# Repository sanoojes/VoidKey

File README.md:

# VoidKey

A Security key with RP2350A

## PCB

Images will be attached soon

## Firmware

A fork of the [pico-fido](https://github.com/polhenarejos/pico-fido) for this
project [pico-fido-voidkey](https://github.com/sanoojes/pico-fido-voidkey)

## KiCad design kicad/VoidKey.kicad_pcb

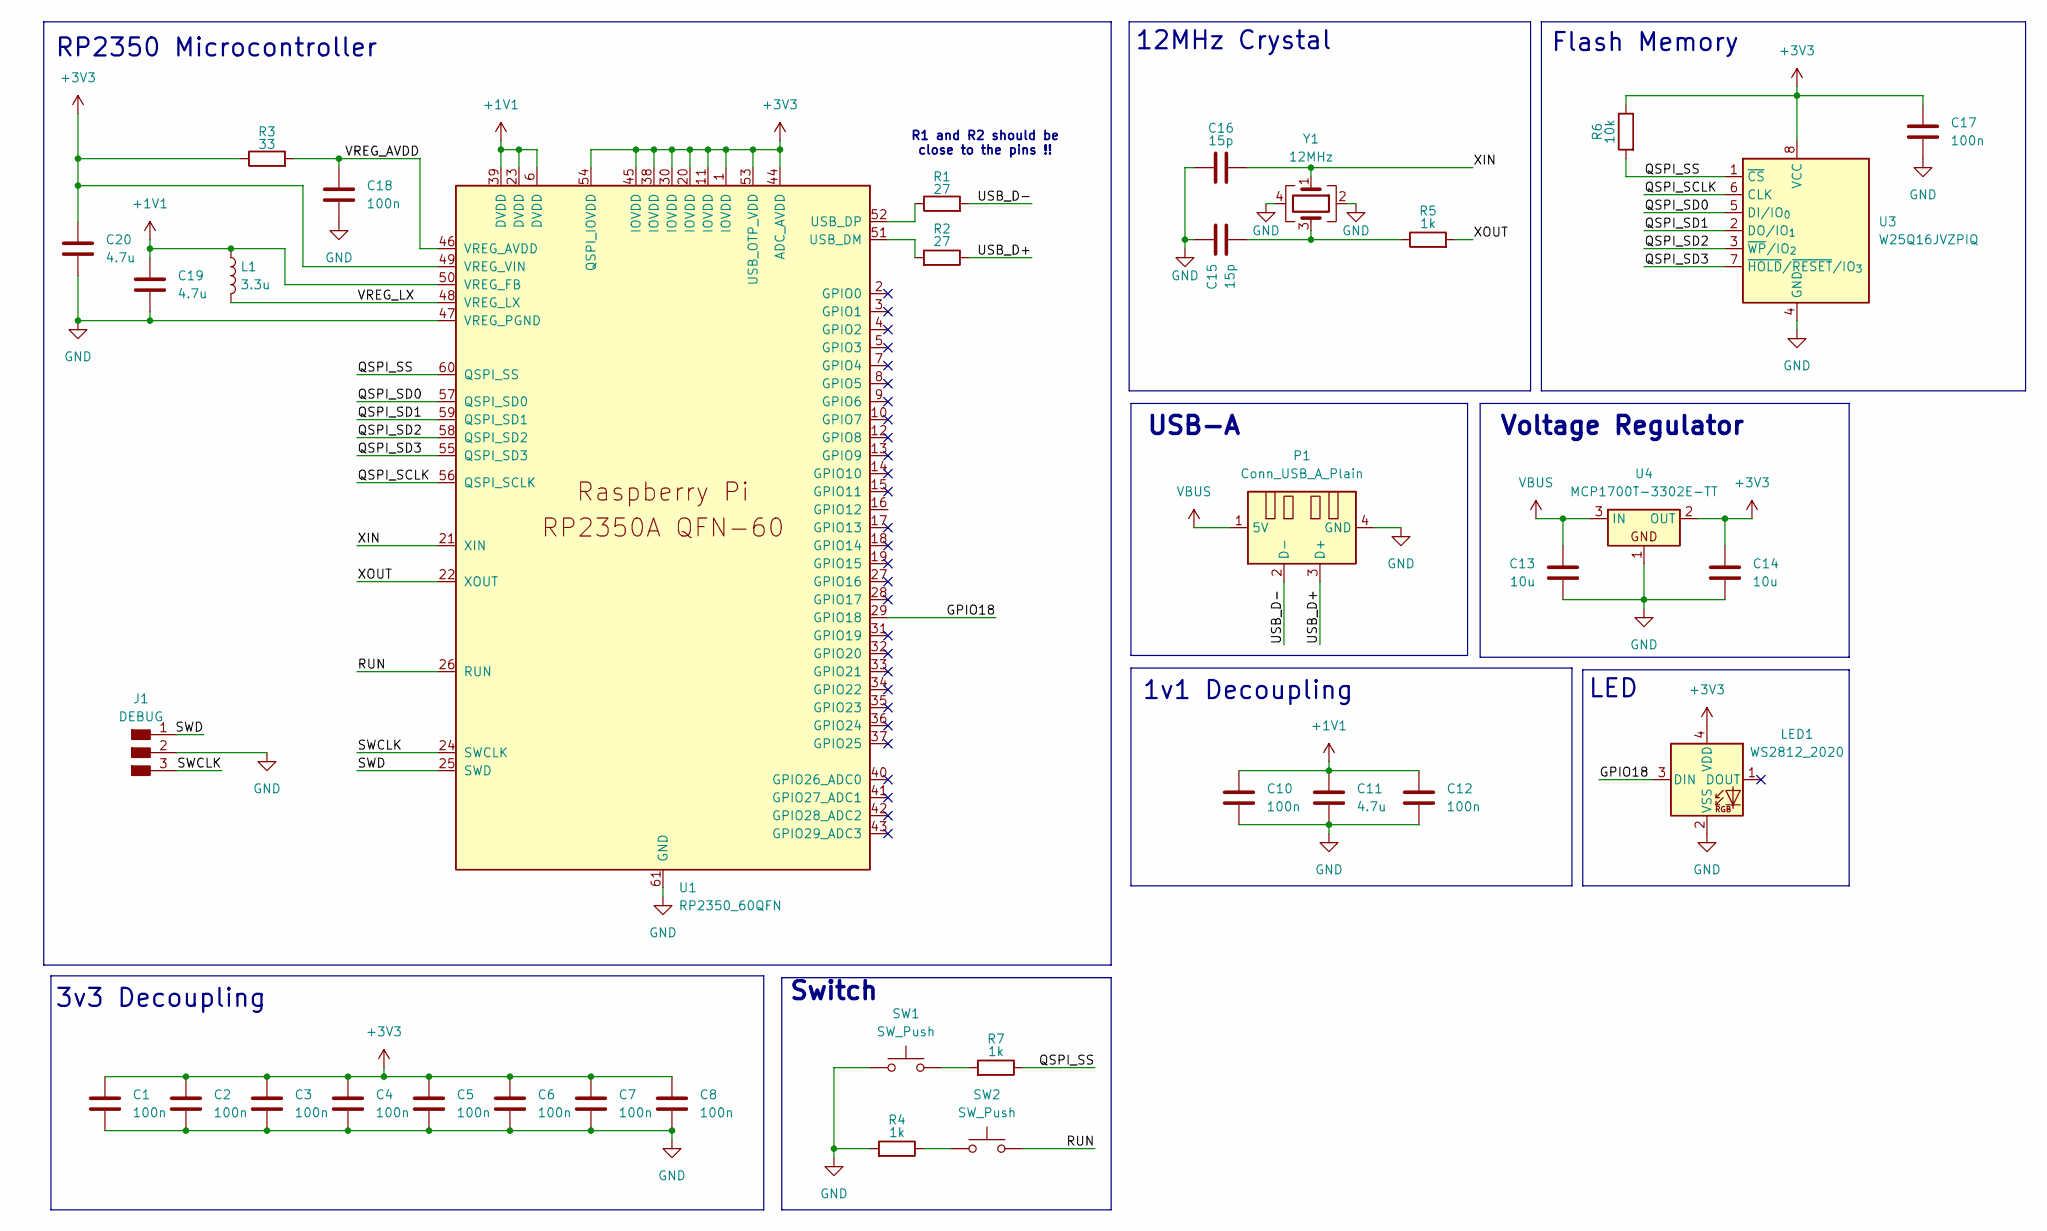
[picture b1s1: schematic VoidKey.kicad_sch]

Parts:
C1, C2, C3, C4, C5, C6, C7, C8, C10, C12, C17, C18: 100n; C_0402_1005Metric
C11, C19, C20: 4.7u; C_0402_1005Metric
C13, C14: 10u; C_0402_1005Metric
C15, C16: 15p; C_0402_1005Metric
J1: DEBUG; PinHeader_01x03_P2.54mm_Vertical_THT_D1mm
L1: 3.3u; L_pol_2016
LED1: WS2812_2020; LED_WS2812_2020
P1: Conn_USB_A_Plain
R1, R2: 27; R_0402_1005Metric
R3: 33; R_0402_1005Metric
R4, R5, R7: 1k; R_0402_1005Metric
R6: 10k; R_0402_1005Metric
SW1, SW2: SW_Push; SW_Push_SPST_NO_Alps_SKRK
U1: RP2350_60QFN; RP2350-QFN-60-1EP_7x7_P0.4mm_EP3.4x3.4mm_ThermalVias
U3: W25Q16JVZPIQ; Winbond_USON-8-1EP_3x2mm_P0.5mm_EP0.2x1.6mm
U4: MCP1700T-3302E-TT; SOT-23
Y1: 12MHz; Crystal_SMD_3225-4Pin_3.2x2.5mm

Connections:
+1V1: C10.1, C11.1, C12.1, C19.1, L1.1, U1.6 (DVDD), U1.23 (DVDD), U1.39 (DVDD), U1.50 (VREG_FB)
+3V3: C1.1, C2.1, C3.1, C4.1, C5.1, C6.1, C7.1, C8.1, C14.2, C17.1, C20.1, LED1.4 (VDD), R3.1, R6.1, U1.1 (IOVDD), U1.11 (IOVDD), U1.20 (IOVDD), U1.30 (IOVDD), U1.38 (IOVDD), U1.44 (ADC_AVDD), U1.45 (IOVDD), U1.49 (VREG_VIN), U1.53 (USB_OTP_VDD), U1.54 (QSPI_IOVDD), U3.8 (VCC), U4.2 (OUT)
/GPIO18: LED1.3 (DIN), U1.29 (GPIO18)
/QSPI_SCLK: U1.56 (QSPI_SCLK), U3.6 (CLK)
/QSPI_SD0: U1.57 (QSPI_SD0), U3.5 (DI/IO_{0})
/QSPI_SD1: U1.59 (QSPI_SD1), U3.2 (DO/IO_{1})
/QSPI_SD2: U1.58 (QSPI_SD2), U3.3 (~WP/IO_{2})
/QSPI_SD3: U1.55 (QSPI_SD3), U3.7 (~HOLD/~RESET/IO_{3})
/QSPI_SS: R6.2, R7.1, U1.60 (QSPI_SS), U3.1 (~CS)
/RUN: SW2.1, U1.26 (RUN)
/SWCLK: J1.3, U1.24 (SWCLK)
/SWD: J1.1, U1.25 (SWD)
/USB_D+: P1.3 (D+), R2.1
/USB_D-: P1.2 (D-), R1.2
/VREG_AVDD: C18.1, R3.2, U1.46 (VREG_AVDD)
/VREG_LX: L1.2, U1.48 (VREG_LX)
/XIN: C16.2, U1.21 (XIN), Y1.1
/XOUT: R5.2, U1.22 (XOUT)
GND: C1.2, C2.2, C3.2, C4.2, C5.2, C6.2, C7.2, C8.2, C10.2, C11.2, C12.2, C13.1, C14.1, C15.1, C16.1, C17.2, C18.2, C19.2, C20.2, J1.2, LED1.2 (VSS), P1.4 (GND), R4.2, SW1.1, U1.47 (VREG_PGND), U1.61 (GND), U3.4 (GND), U4.1, Y1.2, Y1.4
unnamed: C15.2, R5.1, Y1.3
unnamed: R4.1, SW2.2
unnamed: R7.2, SW1.2
unnamed: R2.2, U1.51 (USB_DM)
unnamed: R1.1, U1.52 (USB_DP)
VBUS: C13.2, P1.1 (5V), U4.3 (IN)

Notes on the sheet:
Switch
Voltage Regulator
LED
1v1 Decoupling
R1 and R2 should be close to the pins !!
USB-A
12MHz Crystal
RP2350 Microcontroller
3v3 Decoupling
Flash Memory

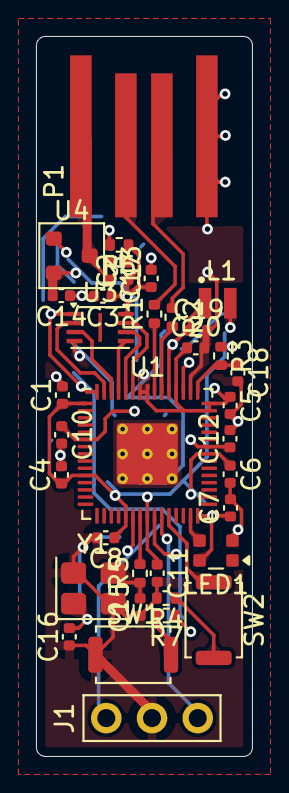
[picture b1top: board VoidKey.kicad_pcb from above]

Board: 2 copper layers, 12.0 x 40.0 mm, 36 parts (0 on the bottom side), 25 nets.

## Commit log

2026-01-04 fix: kicad sheet
